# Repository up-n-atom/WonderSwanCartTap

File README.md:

# USB WonderSwan Cartridge Utility

A WonderSwan cartridge dumper and programmer.

## Prototype

The prototype is being developed on a [vcc-gnd.com](http://vcc-gnd.com) STM32F103ZET6 development board. Although, no longer in production, they're readily available for purchase on [AliExpress](https://www.aliexpress.com/wholesale?SearchText=STM32F103ZET6+Core+Board).

### VCC-GND STM32F103ZET6 Main Board

Details, including photos and schematics are archived at https://stm32-base.org/boards/STM32F103ZET6-VCC-GND-XLarge.html

### VCC-GND STM32F103ZET6 Adapter Boards

The following adapters boards are open-source hardware and designed with [KiCad](https://www.kicad.org/).

* [WonderSwan Cartridge Adapter](/Hardware/vccgnd_f103zet6/WSCarTAdapter)

* [TSOP-48 Adapter](/Hardware/vccgnd_f103zet6/TSOP48Adapter)

### Debug Boards

The following boards are optional and used to facilitate with debugging and reverse engineering.

* [WonderSwan Cartridge Breakout](/Hardware/re/WSCartBreakout)

* [Revolution Probe](https://github.com/up-n-atom/RevP)

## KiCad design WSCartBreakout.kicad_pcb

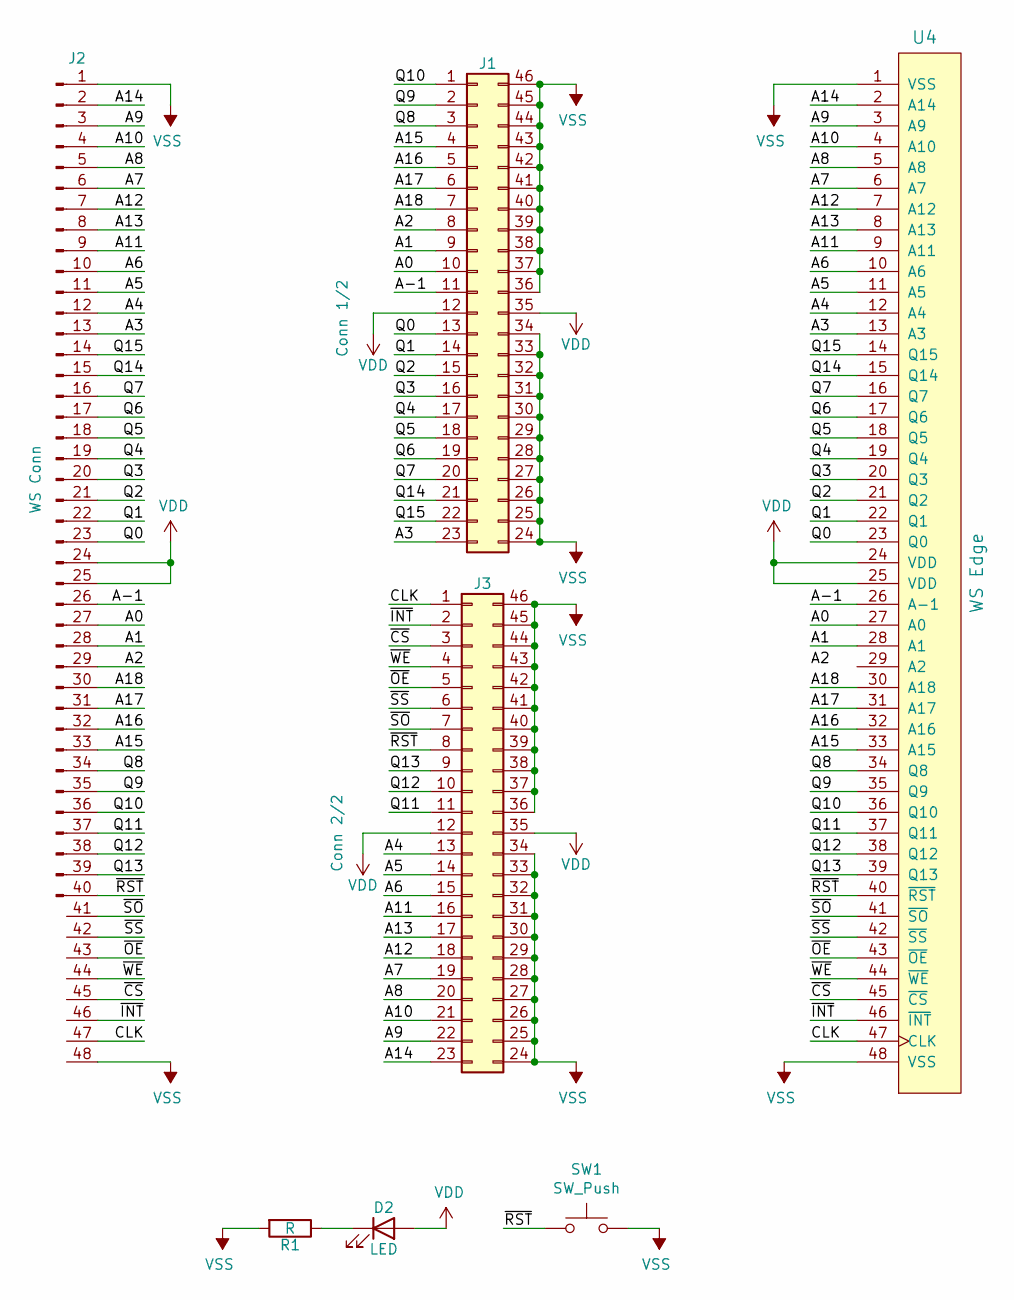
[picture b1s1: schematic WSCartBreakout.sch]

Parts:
D2: LED; LED_0603_1608Metric_Pad1.05x0.95mm_HandSolder
J1: Conn 1/2; Pin_Header_Straight_2x23_Pitch2.54mm_SMD
J2: WS Conn; CONNECTOR
J3: Conn 2/2; Pin_Header_Straight_2x23_Pitch2.54mm_SMD
R1: R; R_0603_1608Metric_Pad1.05x0.95mm_HandSolder
SW1: SW_Push; Panasonic_EVQPUL_EVQPUC
U4: WS Edge; EDGE

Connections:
/A0: J1.10, J2.27, U4.27 (A0)
/A1: J1.9, J2.28, U4.28 (A1)
/A2: J1.8, J2.29
/A3: J1.23, J2.13, U4.13 (A3)
/A4: J2.12, J3.13, U4.12 (A4)
/A5: J2.11, J3.14, U4.11 (A5)
/A6: J2.10, J3.15, U4.10 (A6)
/A7: J2.6, J3.19, U4.6 (A7)
/A8: J2.5, J3.20, U4.5 (A8)
/A9: J2.3, J3.22, U4.3 (A9)
/A10: J2.4, J3.21, U4.4 (A10)
/A11: J2.9, J3.16, U4.9 (A11)
/A12: J2.7, J3.18, U4.7 (A12)
/A13: J2.8, J3.17, U4.8 (A13)
/A14: J2.2, J3.23, U4.2 (A14)
/A15: J1.4, J2.33, U4.33 (A15)
/A16: J1.5, J2.32, U4.32 (A16)
/A17: J1.6, J2.31, U4.31 (A17)
/A18: J1.7, J2.30, U4.30 (A18)
/A-1: J1.11, J2.26, U4.26 (A-1)
/CLK: J2.47, J3.1, U4.47 (CLK)
/Q0: J1.13, J2.23, U4.23 (Q0)
/Q1: J1.14, J2.22, U4.22 (Q1)
/Q2: J1.15, J2.21, U4.21 (Q2)
/Q3: J1.16, J2.20, U4.20 (Q3)
/Q4: J1.17, J2.19, U4.19 (Q4)
/Q5: J1.18, J2.18, U4.18 (Q5)
/Q6: J1.19, J2.17, U4.17 (Q6)
/Q7: J1.20, J2.16, U4.16 (Q7)
/Q8: J1.3, J2.34, U4.34 (Q8)
/Q9: J1.2, J2.35, U4.35 (Q9)
/Q10: J1.1, J2.36, U4.36 (Q10)
/Q11: J2.37, J3.11, U4.37 (Q11)
/Q12: J2.38, J3.10, U4.38 (Q12)
/Q13: J2.39, J3.9, U4.39 (Q13)
/Q14: J1.21, J2.15, U4.15 (Q14)
/Q15: J1.22, J2.14, U4.14 (Q15)
/~CS: J2.45, J3.3, U4.45 (~CS)
/~INT: J2.46, J3.2, U4.46 (~INT)
/~OE: J2.43, J3.5, U4.43 (~OE)
/~RST: J2.40, J3.8, SW1.1, U4.40 (~RST)
/~SO: J2.41, J3.7, U4.41 (~SO)
/~SS: J2.42, J3.6, U4.42 (~SS)
/~WE: J2.44, J3.4, U4.44 (~WE)
unnamed: D2.1 (K), R1.1
VDD: D2.2 (A), J1.12, J1.35, J2.24, J2.25, J3.12, J3.35, U4.24 (VDD), U4.25 (VDD)
VSS: J1.24, J1.25, J1.26, J1.27, J1.28, J1.29, J1.30, J1.31, J1.32, J1.33, J1.34, J1.36, J1.37, J1.38, J1.39, J1.40, J1.41, J1.42, J1.43, J1.44, J1.45, J1.46, J2.1, J2.48, J3.24, J3.25, J3.26, J3.27, J3.28, J3.29, J3.30, J3.31, J3.32, J3.33, J3.34, J3.36, J3.37, J3.38, J3.39, J3.40, J3.41, J3.42, J3.43, J3.44, J3.45, J3.46, R1.2, SW1.2, U4.1 (VSS), U4.48 (VSS)

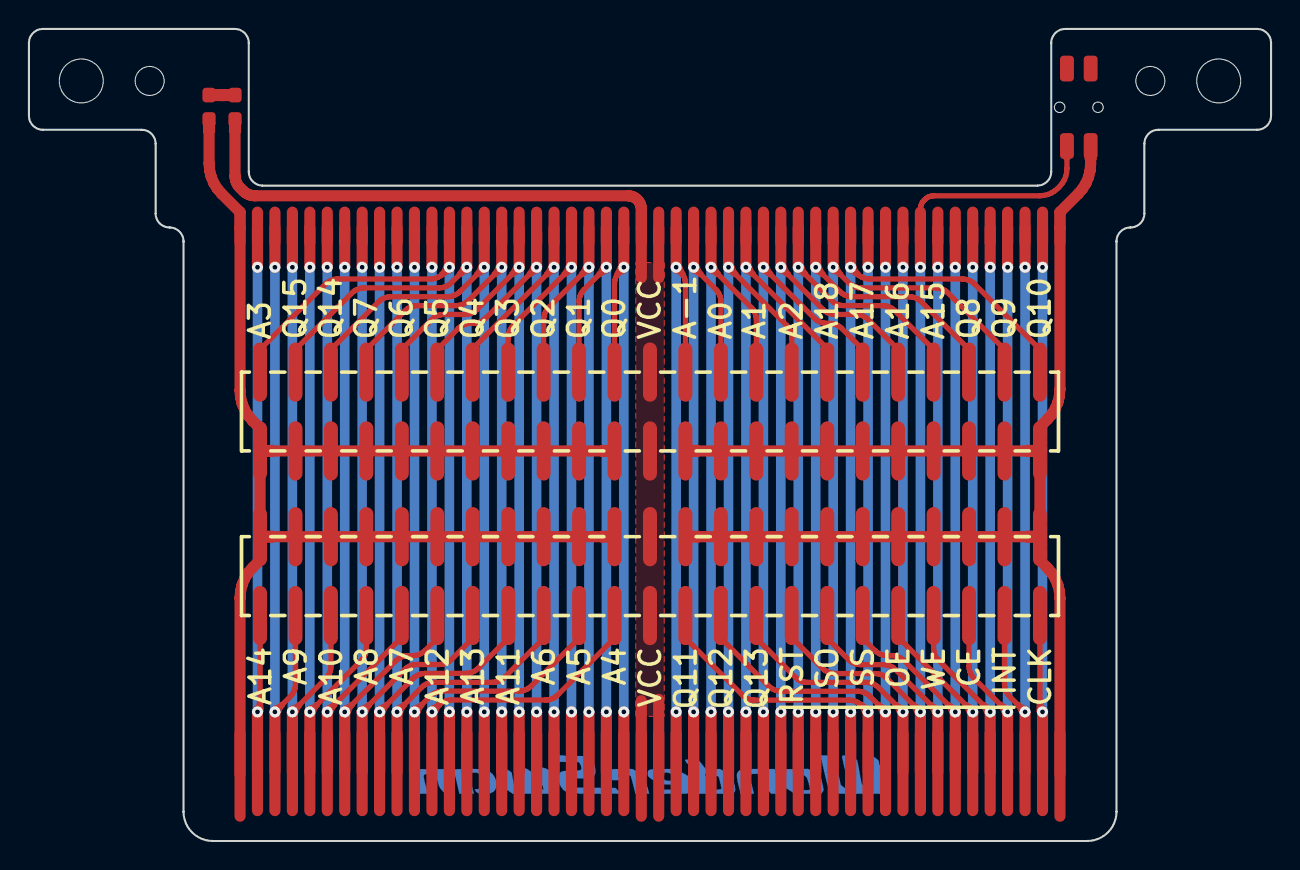
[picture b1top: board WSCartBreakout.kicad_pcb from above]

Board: 2 copper layers, 89.0 x 58.2 mm, 8 parts (1 on the bottom side), 47 nets.

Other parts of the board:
Ref**: Val**; WSLOGO

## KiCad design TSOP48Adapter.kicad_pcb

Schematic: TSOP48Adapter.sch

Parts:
C1, C2: 100nF; C_0805_2012Metric_Pad1.15x1.40mm_HandSolder
J1: Top; PinHeader_2x33_P2.54mm_Vertical
J2: Bottom; PinHeader_2x33_P2.54mm_Vertical
J3: MBM29DL400TC; IC354-048-D31_35P
R1, R2, R3, R4, R5: 10K; R_0805_2012Metric_Pad1.15x1.40mm_HandSolder

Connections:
/5VIN: J2.65
/GND: C1.1, C2.2, J1.1, J1.2, J1.59, J1.61, J1.63, J1.65, J2.2, J2.4, J2.61, J2.62, J2.63, J2.64, J2.66; also elsewhere on the board
/PA0: J1.28
/PA1: J1.29
/PA2: J1.30
/PA3: J1.31
/PA4: J1.32
/PA5: J1.33
/PA6: J1.34
/PA7: J1.35
/PA8: J2.37
/PA9: J2.36
/PA10: J2.35
/PA11: J2.34
/PA12: J2.33
/PA13: J2.32
/PA14: J2.31
/PA15: J2.30
/PB0: J1.38
/PB1: J1.39
/PB2: J1.40
/PB3: J2.11
/PB4: J2.10
/PB5: J2.9
/PB6: J2.8
/PB7: J2.7
/PB8: J2.6
/PB9: J2.5
/PB10: J1.57
/PB11: J1.58
/PB12: J2.60
/PB13: J2.59
/PB14: J2.58
/PB15: J2.57
/PC0: J1.24
/PC1: J1.25
/PC2: J1.26
/PC3: J1.27
/PC4: J1.36
/PC5: J1.37
/PC6: J2.41
/PC7: J2.40
/PC8: J2.39
/PC9: J2.38
/PC10: J2.29
/PC11: J2.28
/PC12: J2.27
/PC13: J1.10
/PC14: J1.11
/PC15: J1.12
/PD0: J2.26; also elsewhere on the board
/PD1: J2.25; also elsewhere on the board
/PD2: J2.24
/PD3: J2.23
/PD4: J2.22; also elsewhere on the board
/PD5: J2.21; also elsewhere on the board
/PD6: J2.20, R5.2; also elsewhere on the board
/PD7: J2.19
/PD8: J2.56; also elsewhere on the board
/PD9: J2.55; also elsewhere on the board
/PD10: J2.54; also elsewhere on the board
/PD11: J2.53; also elsewhere on the board
/PD12: J2.52; also elsewhere on the board
/PD13: J2.51; also elsewhere on the board
/PD14: J2.50; also elsewhere on the board
/PD15: J2.49; also elsewhere on the board
/PE0: J1.3
/PE1: J1.4
/PE2: J1.5
/PE3: J1.6; also elsewhere on the board
/PE4: J1.7; also elsewhere on the board
/PE5: J1.8; also elsewhere on the board
/PE6: J1.9
/PE7: J1.48; also elsewhere on the board
/PE8: J1.49; also elsewhere on the board
/PE9: J1.50; also elsewhere on the board
/PE10: J1.51; also elsewhere on the board
/PE11: J1.52; also elsewhere on the board
/PE12: J1.53; also elsewhere on the board
/PE13: J1.54; also elsewhere on the board
/PE14: J1.55; also elsewhere on the board
/PE15: J1.56; also elsewhere on the board
/PF0: J1.13; also elsewhere on the board
/PF1: J1.14; also elsewhere on the board
/PF2: J1.15; also elsewhere on the board
/PF3: J1.16; also elsewhere on the board
/PF4: J1.17; also elsewhere on the board
/PF5: J1.18; also elsewhere on the board
/PF6: J1.19
/PF7: J1.20
/PF8: J1.21
/PF9: J1.22
/PF10: J1.23
/PF11: J1.41
/PF12: J1.42; also elsewhere on the board
/PF13: J1.43; also elsewhere on the board
/PF14: J1.44; also elsewhere on the board
/PF15: J1.45; also elsewhere on the board
/PG0: J1.46; also elsewhere on the board
/PG1: J1.47; also elsewhere on the board
/PG2: J2.48; also elsewhere on the board
/PG3: J2.47; also elsewhere on the board
/PG4: J2.46; also elsewhere on the board
/PG5: J2.45; also elsewhere on the board
/PG6: J2.44
/PG7: J2.43
/PG8: J2.42
/PG9: J2.18, R4.2; also elsewhere on the board
/PG10: J2.17
/PG11: J2.16
/PG12: J2.15
/PG13: J2.14
/PG14: J2.13
/PG15: J2.12
/VBAT: J2.3
/VCC: C2.1, J1.60, J1.62, J1.64, J1.66, J2.1, R1.2, R2.1, R3.1, R4.1, R5.1; also elsewhere on the board
unnamed 116: C1.2, R1.1; also elsewhere on the board
unnamed 117: R2.2; also elsewhere on the board
unnamed 118: R3.2; also elsewhere on the board

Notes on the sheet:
STM32F103ZET6

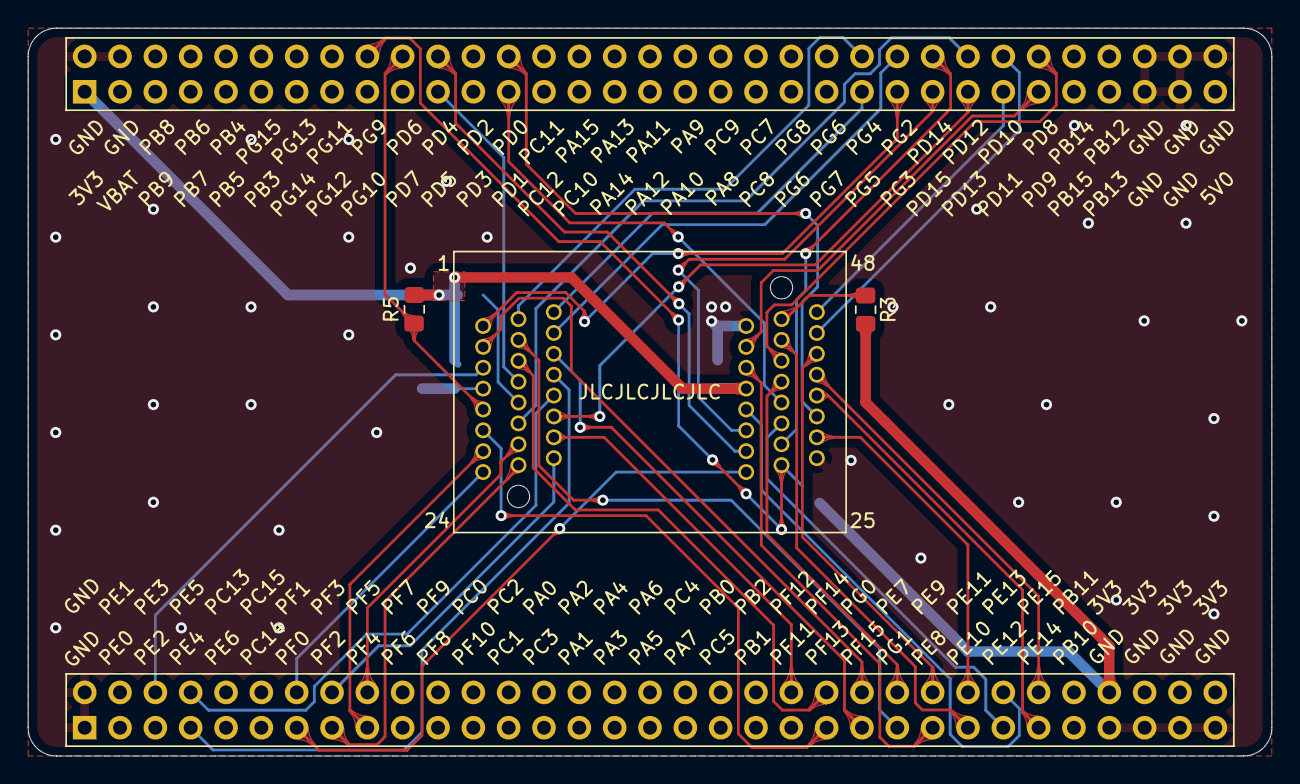
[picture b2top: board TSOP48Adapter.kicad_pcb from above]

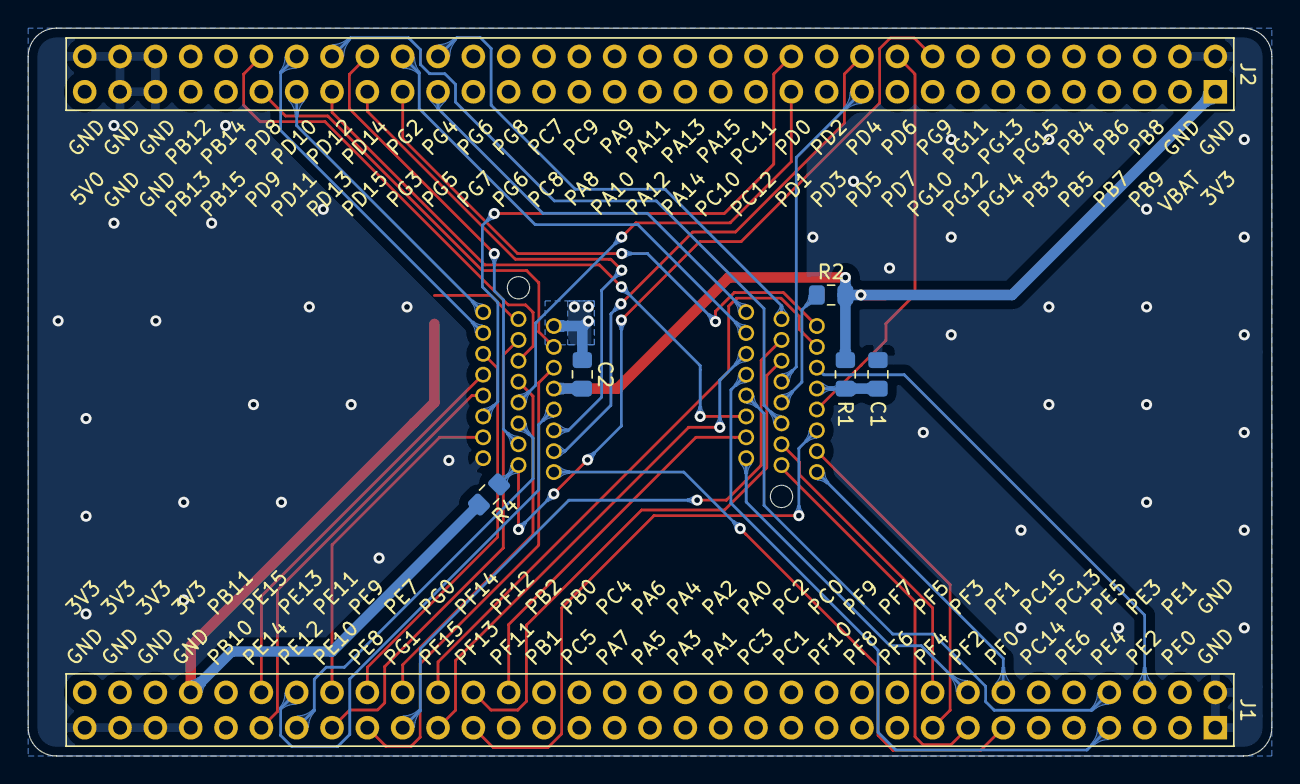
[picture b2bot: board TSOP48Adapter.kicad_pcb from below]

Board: 2 copper layers, 89.4 x 52.3 mm, 10 parts (5 on the bottom side), 47 nets.

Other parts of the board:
JLCJLCJLCJLC: MBM29DL400TC; IC354-048-D31_35P

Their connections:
/GND: JLCJLCJLCJLC.27, JLCJLCJLCJLC.46; also elsewhere on the board
/PD0: JLCJLCJLCJLC.33; also elsewhere on the board
/PD1: JLCJLCJLCJLC.35; also elsewhere on the board
/PD4: JLCJLCJLCJLC.28; also elsewhere on the board
/PD5: JLCJLCJLCJLC.11; also elsewhere on the board
/PD6: JLCJLCJLCJLC.15; also elsewhere on the board
/PD8: JLCJLCJLCJLC.41; also elsewhere on the board
/PD9: JLCJLCJLCJLC.43; also elsewhere on the board
/PD10: JLCJLCJLCJLC.45; also elsewhere on the board
/PD11: JLCJLCJLCJLC.48; also elsewhere on the board
/PD12: JLCJLCJLCJLC.17; also elsewhere on the board
/PD13: JLCJLCJLCJLC.16; also elsewhere on the board
/PD14: JLCJLCJLCJLC.29; also elsewhere on the board
/PD15: JLCJLCJLCJLC.31; also elsewhere on the board
/PE3: JLCJLCJLCJLC.9; also elsewhere on the board
/PE4: JLCJLCJLCJLC.10; also elsewhere on the board
/PE5: JLCJLCJLCJLC.13; also elsewhere on the board
/PE7: JLCJLCJLCJLC.38; also elsewhere on the board
/PE8: JLCJLCJLCJLC.40; also elsewhere on the board
/PE9: JLCJLCJLCJLC.42; also elsewhere on the board
/PE10: JLCJLCJLCJLC.44; also elsewhere on the board
/PE11: JLCJLCJLCJLC.30; also elsewhere on the board
/PE12: JLCJLCJLCJLC.32; also elsewhere on the board
/PE13: JLCJLCJLCJLC.34; also elsewhere on the board
/PE14: JLCJLCJLCJLC.36; also elsewhere on the board
/PE15: JLCJLCJLCJLC.39; also elsewhere on the board
/PF0: JLCJLCJLCJLC.25; also elsewhere on the board
/PF1: JLCJLCJLCJLC.24; also elsewhere on the board
/PF2: JLCJLCJLCJLC.23; also elsewhere on the board
/PF3: JLCJLCJLCJLC.22; also elsewhere on the board
/PF4: JLCJLCJLCJLC.21; also elsewhere on the board
/PF5: JLCJLCJLCJLC.20; also elsewhere on the board
/PF12: JLCJLCJLCJLC.19; also elsewhere on the board
/PF13: JLCJLCJLCJLC.18; also elsewhere on the board
/PF14: JLCJLCJLCJLC.8; also elsewhere on the board
/PF15: JLCJLCJLCJLC.7; also elsewhere on the board
/PG0: JLCJLCJLCJLC.6; also elsewhere on the board
/PG1: JLCJLCJLCJLC.5; also elsewhere on the board
/PG2: JLCJLCJLCJLC.4; also elsewhere on the board
/PG3: JLCJLCJLCJLC.3; also elsewhere on the board
/PG4: JLCJLCJLCJLC.2; also elsewhere on the board
/PG5: JLCJLCJLCJLC.1; also elsewhere on the board
/PG9: JLCJLCJLCJLC.26; also elsewhere on the board
/VCC: JLCJLCJLCJLC.37; also elsewhere on the board
unnamed 116: JLCJLCJLCJLC.12; also elsewhere on the board
unnamed 117: JLCJLCJLCJLC.14; also elsewhere on the board
unnamed 118: JLCJLCJLCJLC.47; also elsewhere on the board

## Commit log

2021-11-04 Add terminating newline to .gitignore
2021-11-04 Remove ignored files
2021-11-04 Add terminating newline
2021-11-05 Fix USB descriptors
2021-11-06 Complete volatile buffer cleanse
2021-11-08 Use localized naming
2021-11-08 Define control buffer size
2021-11-09 Remove USD DFU detach attribute
2021-11-09 Clear USB DFU detach timeout
2021-11-11 Fix reversed FSMC enable and disable logic
2021-11-11 Fix NOR address verification
2021-11-11 Check 2-byte alignment of NOR address in FSMC 16-bit mode
2021-11-11 Fix MBC STRICT case
2021-11-11 Remove unnecessary mask from cast
2021-11-11 Remove sleep after GPIO edge transition
2021-11-11 Add FSMC bus width convenience functions
2021-11-11 Add missing control buffer size definition
2021-11-11 Add USB TAP interface
2021-11-11 Add TAP handshake and dump header control requests
2021-11-12 Remove USB DFU interface
2021-11-12 Remove Software
2021-11-12 Prevent 0 cycle delay race
2021-11-12 Increase USB max packet size
2021-11-12 Set return buffer length
2021-11-12 Fix whitespace ie. tabs to spaces
2021-11-12 Get unique serial number
2021-11-12 Handle TAP port poke and peek
2021-11-12 Reduce whitespace
2021-11-12 Modify TAP request protocol
2021-11-12 Clear TAP buffer prior to mbc peek
2021-11-13 Fix FSMC reset values
2021-11-13 Disable FSMC bank1
2021-11-13 Enable and use FSMC extended mode C
2021-11-13 Clean FSMC reset
2021-11-13 Fix 16-bit SRAM addressing
2021-11-13 Fix TAP port peek and poke
2021-11-13 Add TAP ram peek and poke
2021-11-13 Remove superfluous header
2021-11-13 Modify TAP requests
2021-11-13 Reorganize TAP switch
2021-11-13 Use control complete callback typedef
2021-11-13 Use GCC unused attribute
2021-11-13 Add TAP rom0/1 peek
2021-11-13 Fix TAP rom0/1 peek addressing
2021-11-14 Enhance TAP spec with inspiration from DFU
2021-11-14 Use appropriately sized indexer
2021-11-14 Ignore requests until error acknowledged
2021-11-15 Clean up addressing
2021-11-15 Add cartridge header structure
2021-11-16 Fix cart header structure
    Applies the packed attribute to the structure and corrects endianness
2021-11-16 Add TAP dump ROM
2021-11-16 Clean-up TAP buffer
2021-11-17 Check ROM size
    Prevent an out-of-bounds exception
2021-11-17 Fix code style
2021-11-17 Re-introduce TAP error state check
2021-11-17 Rejig TAP dump ROM
2021-11-17 Set return length zero in TAP error state
2021-11-17 Add TAP dump RAM
2021-11-17 Move sizing tables to header
2021-11-17 Rename size tables
2021-11-17 Use sizeof rather than constants
2021-11-17 Replace missed fixed values
2021-11-17 Move TAP dump rom/ram logic from switch to functions
2021-11-17 TAP dump header return size
2021-11-17 Return zero length on TAP dump error
2021-11-17 Ignore return value
2021-11-17 Pass length to TAP dump functions
2021-11-17 Fix state when clearing error
2021-11-17 Set length to zero on error within TAP poke
2021-11-18 Clean up TAP rom and ram dump logic
2021-11-18 Use FSMC extended mode A
2021-11-18 Fix LED inline declarations
2021-11-18 Add LED toggle on cartridge detection
2021-11-22 Cleanup TAP dump header
2021-11-22 Use external clock source
2021-11-22 Rename sleep preprocessor definition
2021-11-22 Expand comment
2021-11-23 Add warning message when using HSI clock source with USB peripheral
2021-12-06 Add WinUSB support
    Microsoft OS 1.0 descriptors
2021-12-06 Misc. code clean-up
2021-12-06 Add interface comment
2021-12-06 Update PlatformIO tasks
2021-12-07 Clean-up USB setup
2021-12-07 Use built-in WFI function
2021-12-07 Remove superfluous includes
2021-12-07 Add USB suspend with stop mode
2021-12-07 Add libopencm3 comment for PlatformIO
    PlatformIO supplies the stable 0.8.0 api
2021-12-07 Fix function order for stop mode
2021-12-07 Move and clean-up app logic
2021-12-08 Fix winusb header definition naming
2021-12-08 Clean-up imported winusb_defs header
2021-12-08 Seperate LED and platform
2021-12-08 Check STOP_MODE for debugging during wfi
2021-12-08 Fix pre-processor check
2021-12-08 Let cartridge detection setup the LED
2021-12-08 Clean-up usb code
2022-01-14 Move platform init back to main
2022-01-14 Define region size
    One less magic number
2022-01-14 Use defined identifier
